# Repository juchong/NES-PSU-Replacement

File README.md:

# NES-PSU-Replacement
A replacement NES PSU board that implements a modern switching regulator.

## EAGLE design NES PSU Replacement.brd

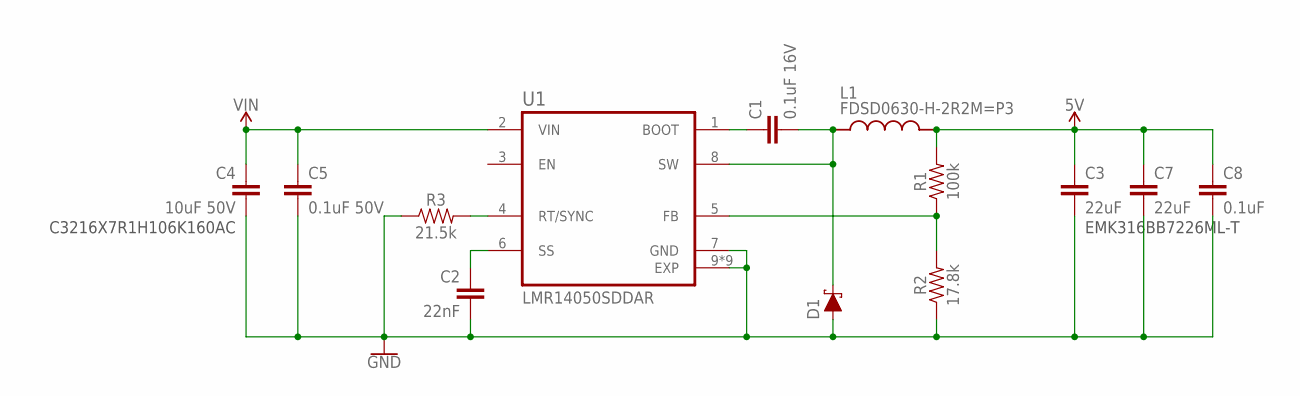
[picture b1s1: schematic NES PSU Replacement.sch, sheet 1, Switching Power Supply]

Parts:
C1: 0.1uF 16V; 0603
C2: 22nF; 0603
C3, C7: 22uF; 1206
C4: 10uF 50V; 1206
C5: 0.1uF 50V; 0603
C8: 0.1uF; 0603
D1: 1A/15V/220mV; DO-214AB
L1: FDSD0630-H-2R2M=P3; IND_FDSD0630-H-2R2M=P3
R1: 100k; 0603
R2: 17.8k; 0603
R3: 21.5k; 0603
U1: LMR14050SDDAR; VREG_LM5017MR/NOPB

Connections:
5V: C3.1, C7.1, C8.1, L1.2, R1.2; also elsewhere on the board
GND: C2.2, C3.2, C4.2, C5.2, C7.2, C8.2, D1.2 (A), R2.1, R3.1, U1.7 (GND), U1.9 (EXP), U1.10 (EXP), U1.11 (EXP), U1.12 (EXP), U1.13 (EXP), U1.14 (EXP), U1.15 (EXP), U1.16 (EXP), U1.17 (EXP); also elsewhere on the board
unnamed: R1.1, R2.2, U1.5 (FB)
unnamed: R3.2, U1.4 (RT/SYNC)
unnamed: C2.1, U1.6 (SS)
unnamed: C1.2, D1.1 (C), L1.1, U1.8 (SW)
unnamed: C1.1, U1.1 (BOOT)
VIN: C4.1, C5.1, U1.2 (VIN); also elsewhere on the board

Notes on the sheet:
EMK316BB7226ML-T
C3216X7R1H106K160AC

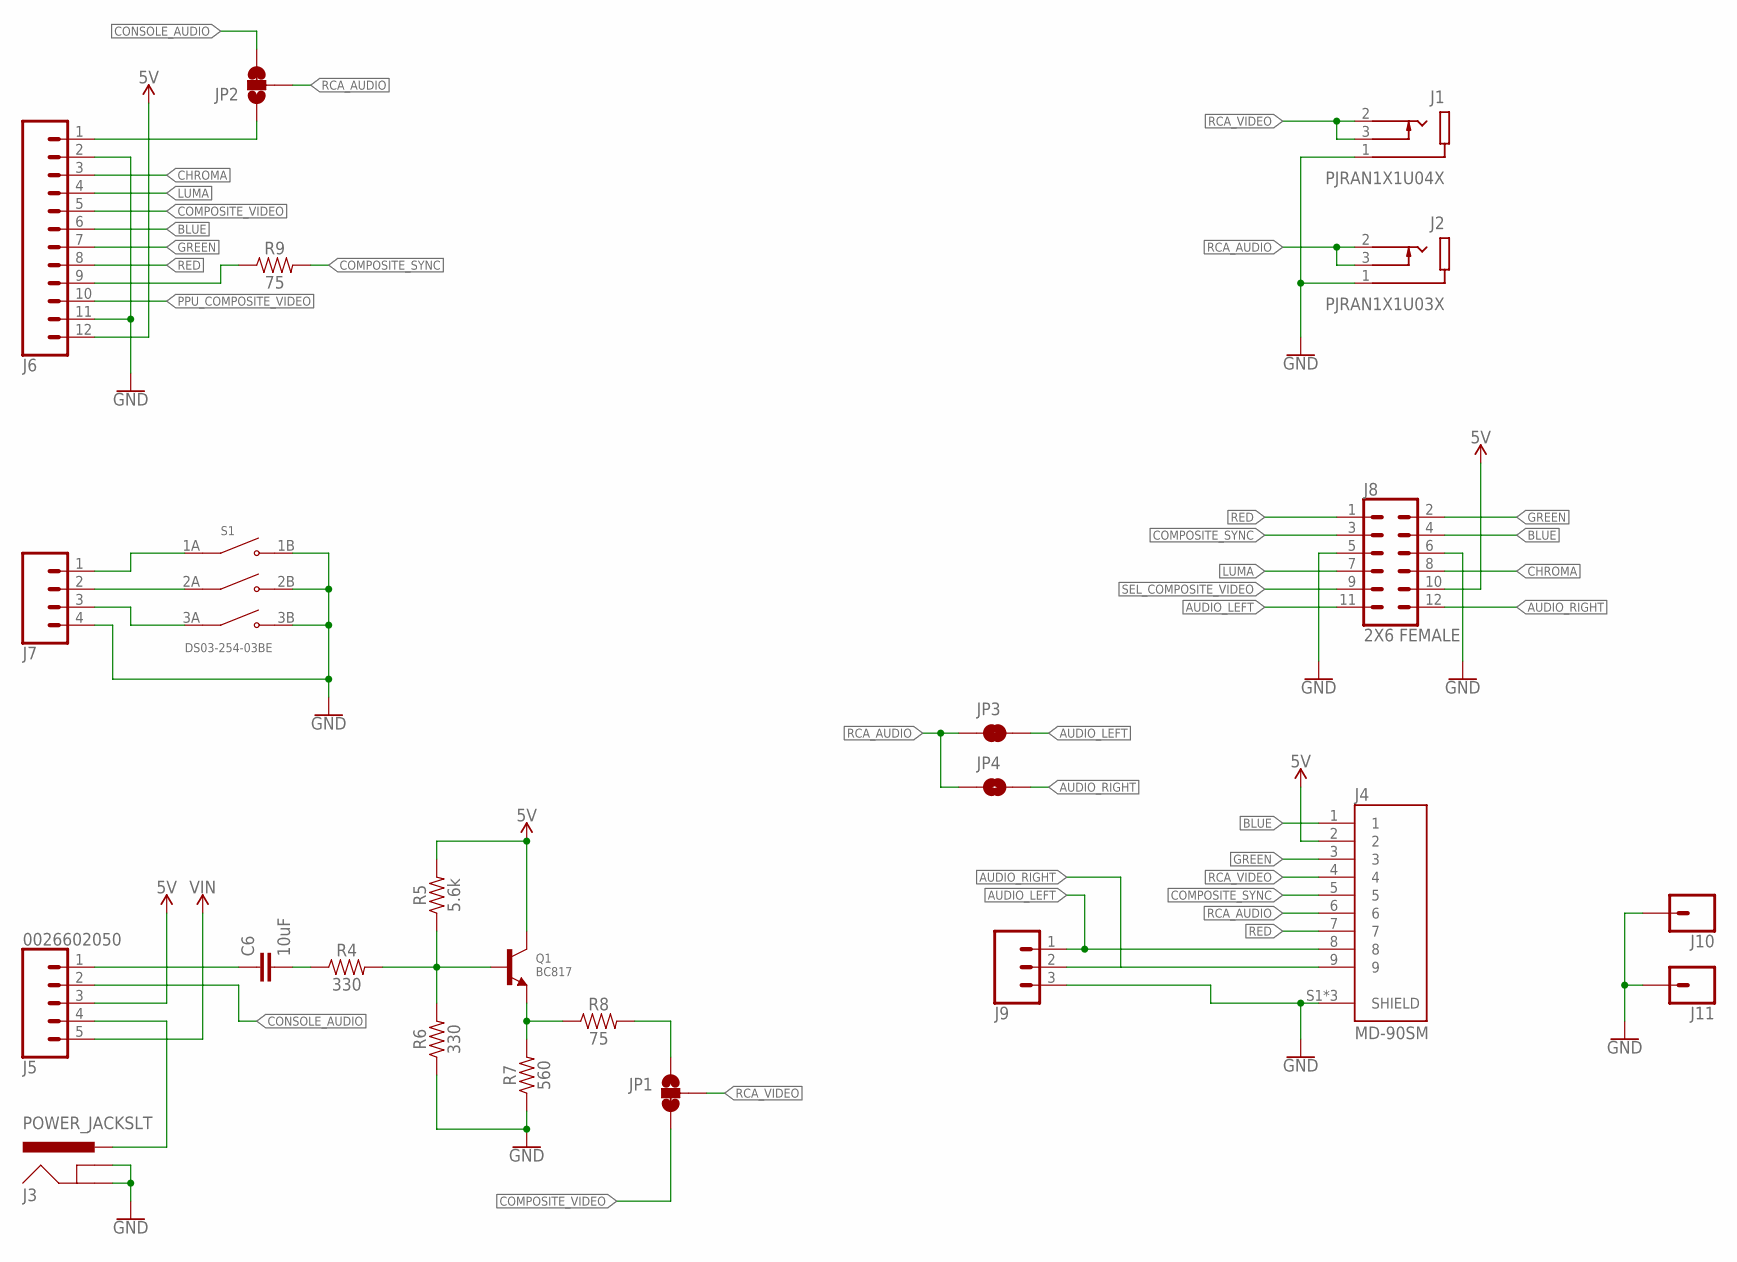
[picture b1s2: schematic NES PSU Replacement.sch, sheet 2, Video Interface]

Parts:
C6: 10uF; 1206
J1: PJRAN1X1U04X; SWITCHCRAFT_PJRAN1X1U02AUX
J2: PJRAN1X1U03X; SWITCHCRAFT_PJRAN1X1U02AUX
J3: POWER_JACKSLT; POWER_JACK_SLOT
J4: MD-90SM; CUI_MD-90SM
J5: 0026602050; 1X05_3.96MM
J6: CONN_12LONGPADS; 1X12_LONGPADS
J7: CONN_04LONGPADS; 1X04_LONGPADS
J8: 2X6 FEMALE; 2X6
J9: CONN_03LONGPADS; 1X03_LONGPADS
J10, J11: CONN_01KEYSTONE_1216; 1X01_1216
JP1, JP2: JUMPER-SMT_3_1-NC_TRACE_SILK; SMT-JUMPER_3_1-NC_TRACE_SILK
JP3: JUMPER-SMT_2_NC_TRACE_SILK; SMT-JUMPER_2_NC_TRACE_SILK
JP4: JUMPER-SMT_2_NO_SILK; SMT-JUMPER_2_NO_SILK
Q1: BC817; SOT23-R
R4, R6: 330; 0603
R5: 5.6k; 0603
R7: 560; 0603
R8, R9: 75; 0603
S1: DS03-254-03BE; SW_DS03-254-03BE

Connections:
5V: J4.2, J5.3, J6.12, J8.10, Q1.3 (C), R5.2; also elsewhere on the board
AUDIO_LEFT: J4.8, J8.11, J9.1, JP3.2
AUDIO_RIGHT: J4.9, J8.12, J9.2, JP4.2
BLUE: J4.1, J6.6, J8.4
CHROMA: J6.3, J8.8
COMPOSITE_SYNC: J4.5, J8.3, R9.2
COMPOSITE_VIDEO: J6.5, JP1.3
CONSOLE_AUDIO: J5.2, JP2.3
GND: J1.1 (SLEEVE), J2.1 (SLEEVE), J3.GND@1 (GNDBREAK), J3.GND@2 (GND), J4.S1 (SHIELD), J4.S2 (SHIELD), J4.S3 (SHIELD), J6.2, J6.11, J7.4, J8.5, J8.6, J9.3, J10.P$1, J10.P$2, J11.P$1, J11.P$2, R6.1, R7.1, S1.1B (NO1), S1.2B (NO2), S1.3B (NO3); also elsewhere on the board
GREEN: J4.3, J6.7, J8.2
LUMA: J6.4, J8.7
unnamed: J7.1, S1.1A (COM1)
unnamed: J7.2, S1.2A (COM2)
unnamed: J7.3, S1.3A (COM3)
unnamed: Q1.1 (B), R4.2, R5.1, R6.2
unnamed: J3.PWR, J5.4
unnamed: JP1.1, R8.2
unnamed: C6.2, R4.1
unnamed: Q1.2 (E), R7.2, R8.1
unnamed: C6.1, J5.1
unnamed: J6.9, R9.1
unnamed: J6.1, JP2.1
PPU_COMPOSITE_VIDEO: J6.10
RCA_AUDIO: J2.2 (TIP), J2.3 (SHUNT), J4.6, JP2.2, JP3.1, JP4.1
RCA_VIDEO: J1.2 (TIP), J1.3 (SHUNT), J4.4, JP1.2
RED: J4.7, J6.8, J8.1
SEL_COMPOSITE_VIDEO: J8.9
VIN: J5.5; also elsewhere on the board

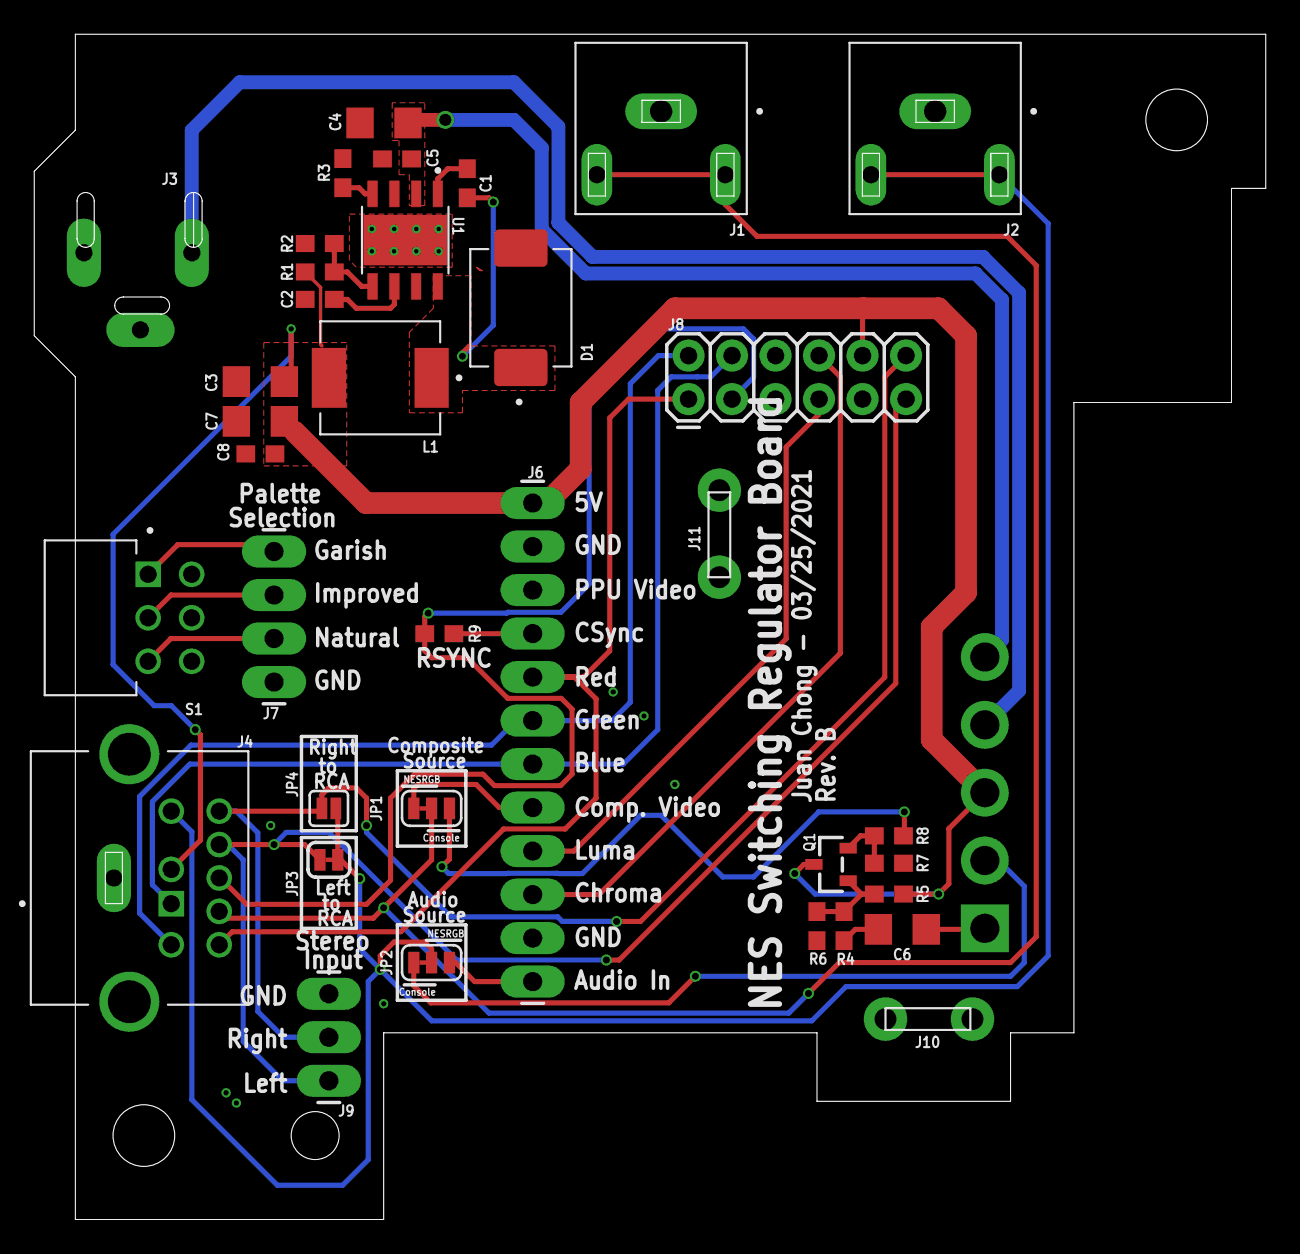
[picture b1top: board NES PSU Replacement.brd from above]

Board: 2 copper layers, 71.9 x 69.2 mm, 37 parts (0 on the bottom side), 31 nets.

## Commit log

2021-03-25 Initial commit. PCB revisions start at RevB
2021-03-25 Moved Eagle files out of the root directory

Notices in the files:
parts and their libraries:
SparkFun-Capacitors: Licensing: Creative Commons ShareAlike 4.0 International - https://creativecommons.org/licenses/by-sa/4.0
microbuilder: This work is placed in the public domain, and may be freely used for commercial and non-commercial work with the following conditions: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
